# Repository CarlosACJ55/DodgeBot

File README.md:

# DodgeBot

<!--  -->
## Youtube Demo Video Links

## Description

Punch-dodging robot project started as a senior design group project for ECE 47700 group 5 at Purdue University.

<!-- ### Project Website

Learn about PunchBot on our Project Website!
Https://engineering.purdue.edu/477grp5/ -->

### Dependencies

* Brains coded in Python 3
  - Packaged with **Poetry**
  - Developped with **Pytest**
  - Ui designed in **tkinter**
* Braum controlled by **STM32F7** programmed in **C**
  - Generated drivers with **STM32CubeMX**
  - Depelopped for **Yaskawa** **SGM7G-30A** & **SGM7G-20A** motors

## Authors

* Yusuf Jarada
* Maximillian Drach
* Ayman Motoda
* Carlos Cotera

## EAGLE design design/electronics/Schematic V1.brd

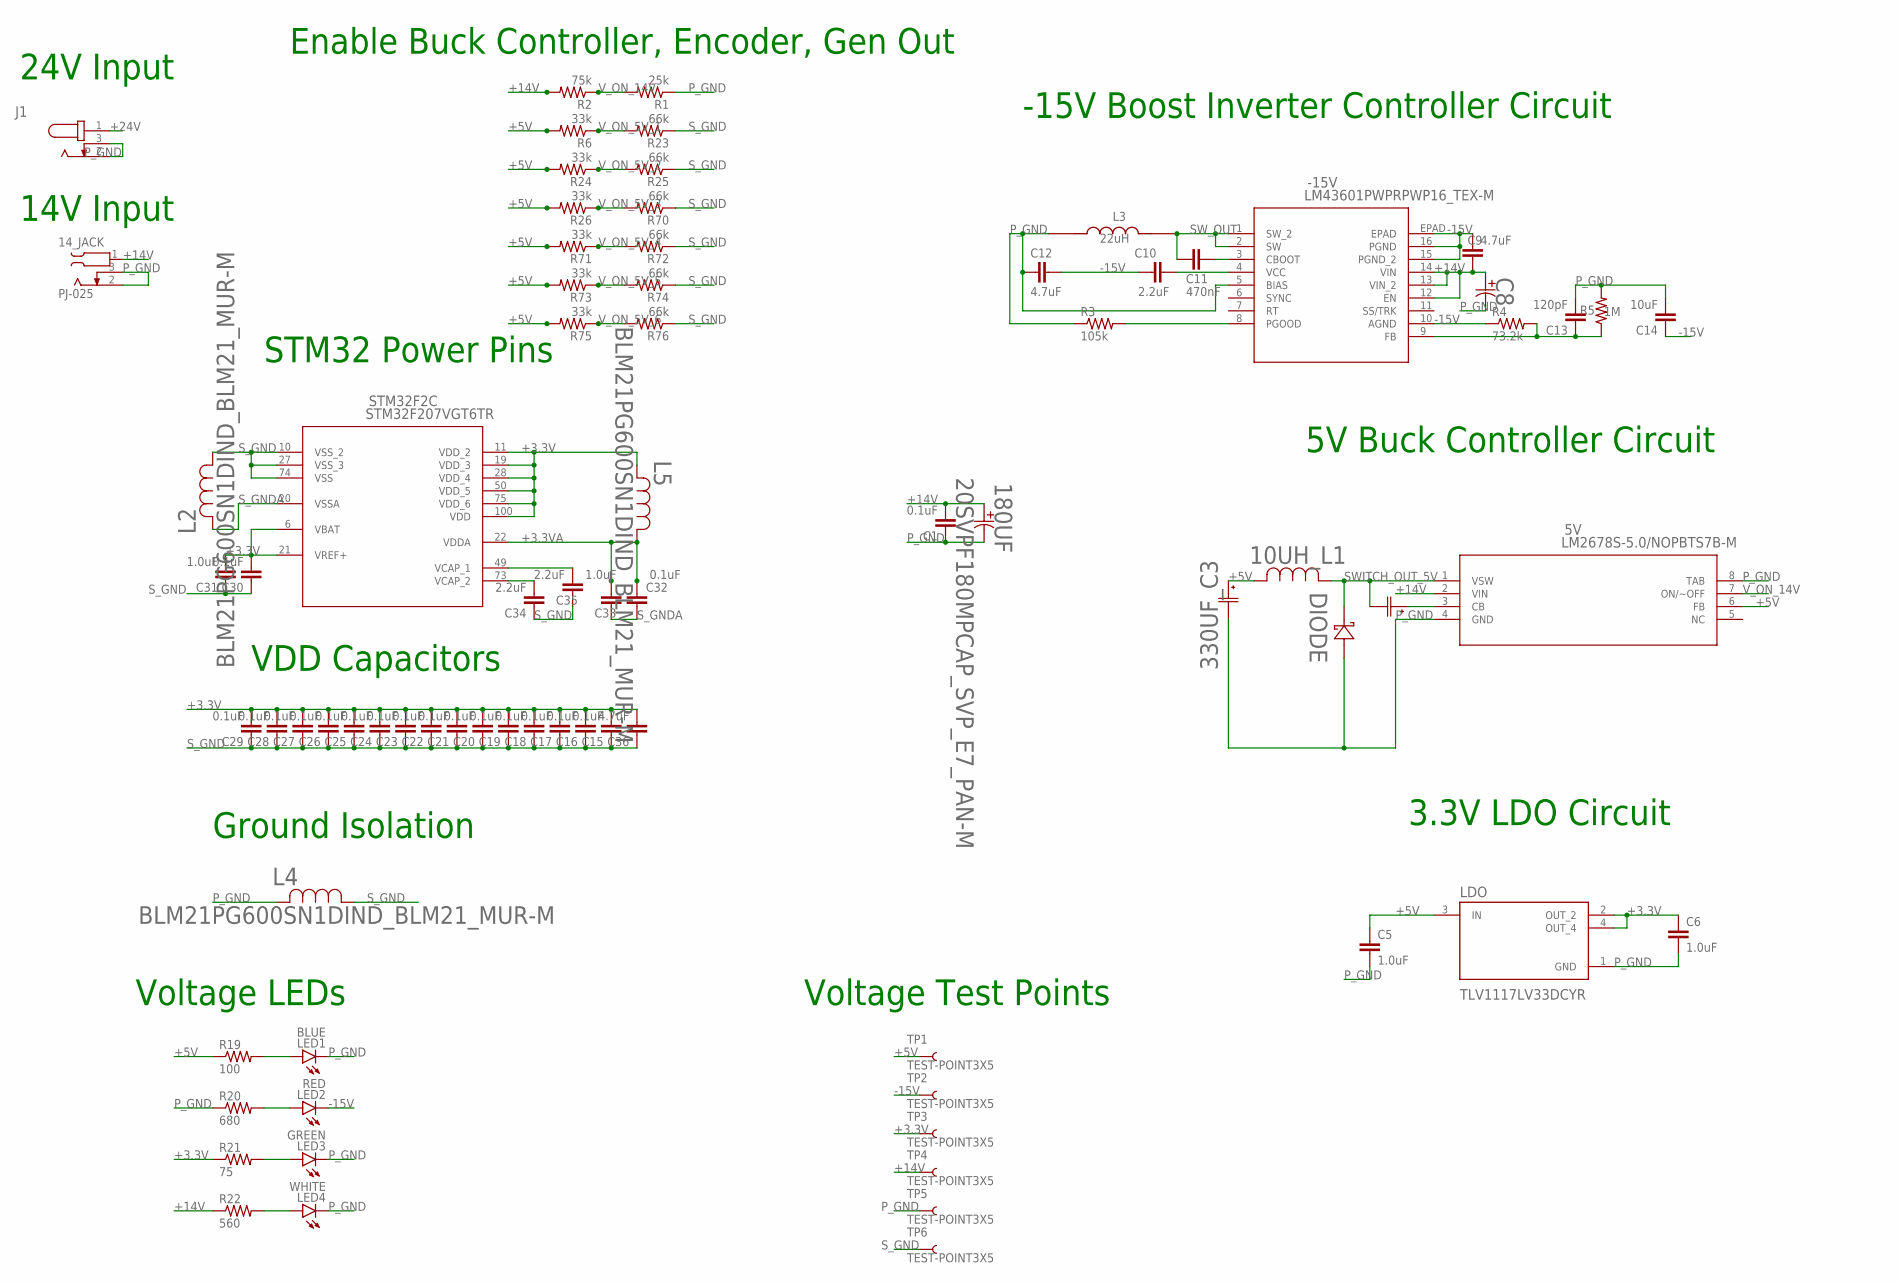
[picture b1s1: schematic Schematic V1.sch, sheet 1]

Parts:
0.01UF_C7: GRM2195C1H103JA01DG-21_MUR-M; G-21_MUR-M
5V: LM2678S-5.0/NOPBTS7B-M; TS7B-M
10UH_L1: SRP1270-100MIND_BOURNS_SRP1270-M; IND_BOURNS_SRP1270-M
14_JACK: PJ-025; CUI_PJ-025
180UF: 20SVPF180MPCAP_SVP_E7_PAN-M; PCAP_SVP_E7_PAN-M
330UF_C3: 10SVPC330MCAP_SVPC_E7_PAN-M; CAP_SVPC_E7_PAN-M
-15V: LM43601PWPRPWP16_TEX-M; PWP16_TEX-M
C1, C15, C16, C17, C18, C19, C20, C21, C22, C23, C24, C25, C26, C27, C28, C29, C30, C32: 0.1uF; 0805
C5, C6, C31, C33: 1.0uF; 0805
C8: 68uF; PCAP_6.3X7.7-ELECT_NCA-M
C9, C12, C36: 4.7uF; 0805
C10, C34, C35: 2.2uF; 0805
C11: 470nF; 0805
C13: 120pF; 0805
C14: 10uF; 0805
DIODE: CDBC520-GCDBC-G-M; CDBC-G-M
J1: PJ-202AH; CUI_PJ-202AH
L2, L4, L5: BLM21PG600SN1DIND_BLM21_MUR-M; IND_BLM21_MUR-M
L3: 22uH; IND_VLS201610CX-220M-1
LDO: TLV1117LV33DCYR; VREG_TLV1117LV33DCYR
LED1: BLUE; CHIPLED_0805
LED2: RED; CHIPLED_0805
LED3: GREEN; CHIPLED_0805
LED4: WHITE; CHIPLED_0805
R1: 25k; R0805
R2: 75k; R0805
R3: 105k; R0805
R4: 73.2k; R0805
R5: 1M; R0805
R6, R24, R26, R71, R73, R75: 33k; R0805
R19: 100; R0805
R20: 680; R0805
R21: 75; R0805
R22: 560; R0805
R23, R25, R70, R72, R74, R76: 66k; R0805
STM32F2: STM32F207VGT6TR; LQFP100-14X14MM
TP1, TP2, TP3, TP4, TP5, TP6: TEST-POINT3X5; PAD.03X.05

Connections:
+3.3V: C6.1, C15.2, C16.2, C17.2, C18.2, C19.2, C20.2, C21.2, C22.2, C23.2, C24.2, C25.2, C26.2, C27.2, C28.2, C29.2, C30.2, C31.2, C36.2, L5.2, LDO.2 (OUT_2), LDO.4 (OUT_4), R21.1, STM32F2.6 (VBAT), STM32F2.11 (VDD_2), STM32F2.19 (VDD_3), STM32F2.21 (VREF+), STM32F2.28 (VDD_4), STM32F2.50 (VDD_5), STM32F2.75 (VDD_6), STM32F2.100 (VDD), TP3.1; also elsewhere on the board
+3.3VA: C32.2, C33.2, L5.1, STM32F2.22 (VDDA)
+5V: 5V.6 (FB), 10UH_L1.2, 330UF_C3.1, C5.1, LDO.3 (IN), R6.2, R19.1, R24.2, R26.2, R71.2, R73.2, R75.2, TP1.1; also elsewhere on the board
+14V: 5V.2 (VIN), 14_JACK.1, 180UF.1, -15V.12 (EN), -15V.13 (VIN_2), -15V.14 (VIN), C1.2, C8.1, C9.2, R2.2, R22.1, TP4.1; also elsewhere on the board
+24V: J1.1; also elsewhere on the board
-15V: -15V.10 (AGND), -15V.15 (PGND_2), -15V.16 (PGND), -15V.EPAD, C9.1, C10.1, C12.1, C14.1, LED2.C, R4.1, TP2.1; also elsewhere on the board
unnamed: -15V.4 (VCC), C10.2
unnamed: 0.01UF_C7.1, 5V.3 (CB)
unnamed: -15V.3 (CBOOT), C11.2
unnamed: C35.2, STM32F2.49 (VCAP_1)
unnamed: C34.2, STM32F2.73 (VCAP_2)
unnamed: -15V.8 (PGOOD), R3.2
unnamed: -15V.9 (FB), C13.1, R4.2, R5.1
unnamed: LED1.A, R19.2
unnamed: LED2.A, R20.2
unnamed: LED3.A, R21.2
unnamed: LED4.A, R22.2
P_GND: 5V.4 (GND), 5V.8 (TAB), 14_JACK.2, 14_JACK.3, 180UF.2, 330UF_C3.2, -15V.5 (BIAS), C1.1, C5.2, C6.2, C8.2, C12.2, C13.2, C14.2, DIODE.2, J1.2, J1.3, L3.1, L4.2, LDO.1 (GND), LED1.C, LED3.C, LED4.C, R1.1, R3.1, R5.2, R20.1, TP5.1; also elsewhere on the board
SWITCH_OUT_5V: 0.01UF_C7.2, 5V.1 (VSW), 10UH_L1.1, DIODE.1
SW_OUT: -15V.1 (SW_2), -15V.2 (SW), C11.1, L3.2
S_GND: C15.1, C16.1, C17.1, C18.1, C19.1, C20.1, C21.1, C22.1, C23.1, C24.1, C25.1, C26.1, C27.1, C28.1, C29.1, C30.1, C31.1, C34.1, C35.1, C36.1, L2.1, L4.1, R23.1, R25.1, R70.1, R72.1, R74.1, R76.1, STM32F2.10 (VSS_2), STM32F2.27 (VSS_3), STM32F2.74 (VSS), TP6.1; also elsewhere on the board
S_GNDA: C32.1, C33.1, L2.2, STM32F2.20 (VSSA)
V_ON_5V_1: R6.1, R23.2; also elsewhere on the board
V_ON_5V_2: R24.1, R25.2; also elsewhere on the board
V_ON_5V_3: R26.1, R70.2; also elsewhere on the board
V_ON_5V_4: R71.1, R72.2; also elsewhere on the board
V_ON_5V_5: R73.1, R74.2; also elsewhere on the board
V_ON_5V_6: R75.1, R76.2; also elsewhere on the board
V_ON_14V: 5V.7 (ON/~OFF), R1.2, R2.1

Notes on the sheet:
VDD Capacitors
STM32 Power Pins
5V Buck Controller Circuit
3.3V LDO Circuit
-15V Boost Inverter Controller Circuit
Enable Buck Controller, Encoder, Gen Out
Ground Isolation
Voltage LEDs
Voltage Test Points
14V Input
24V Input

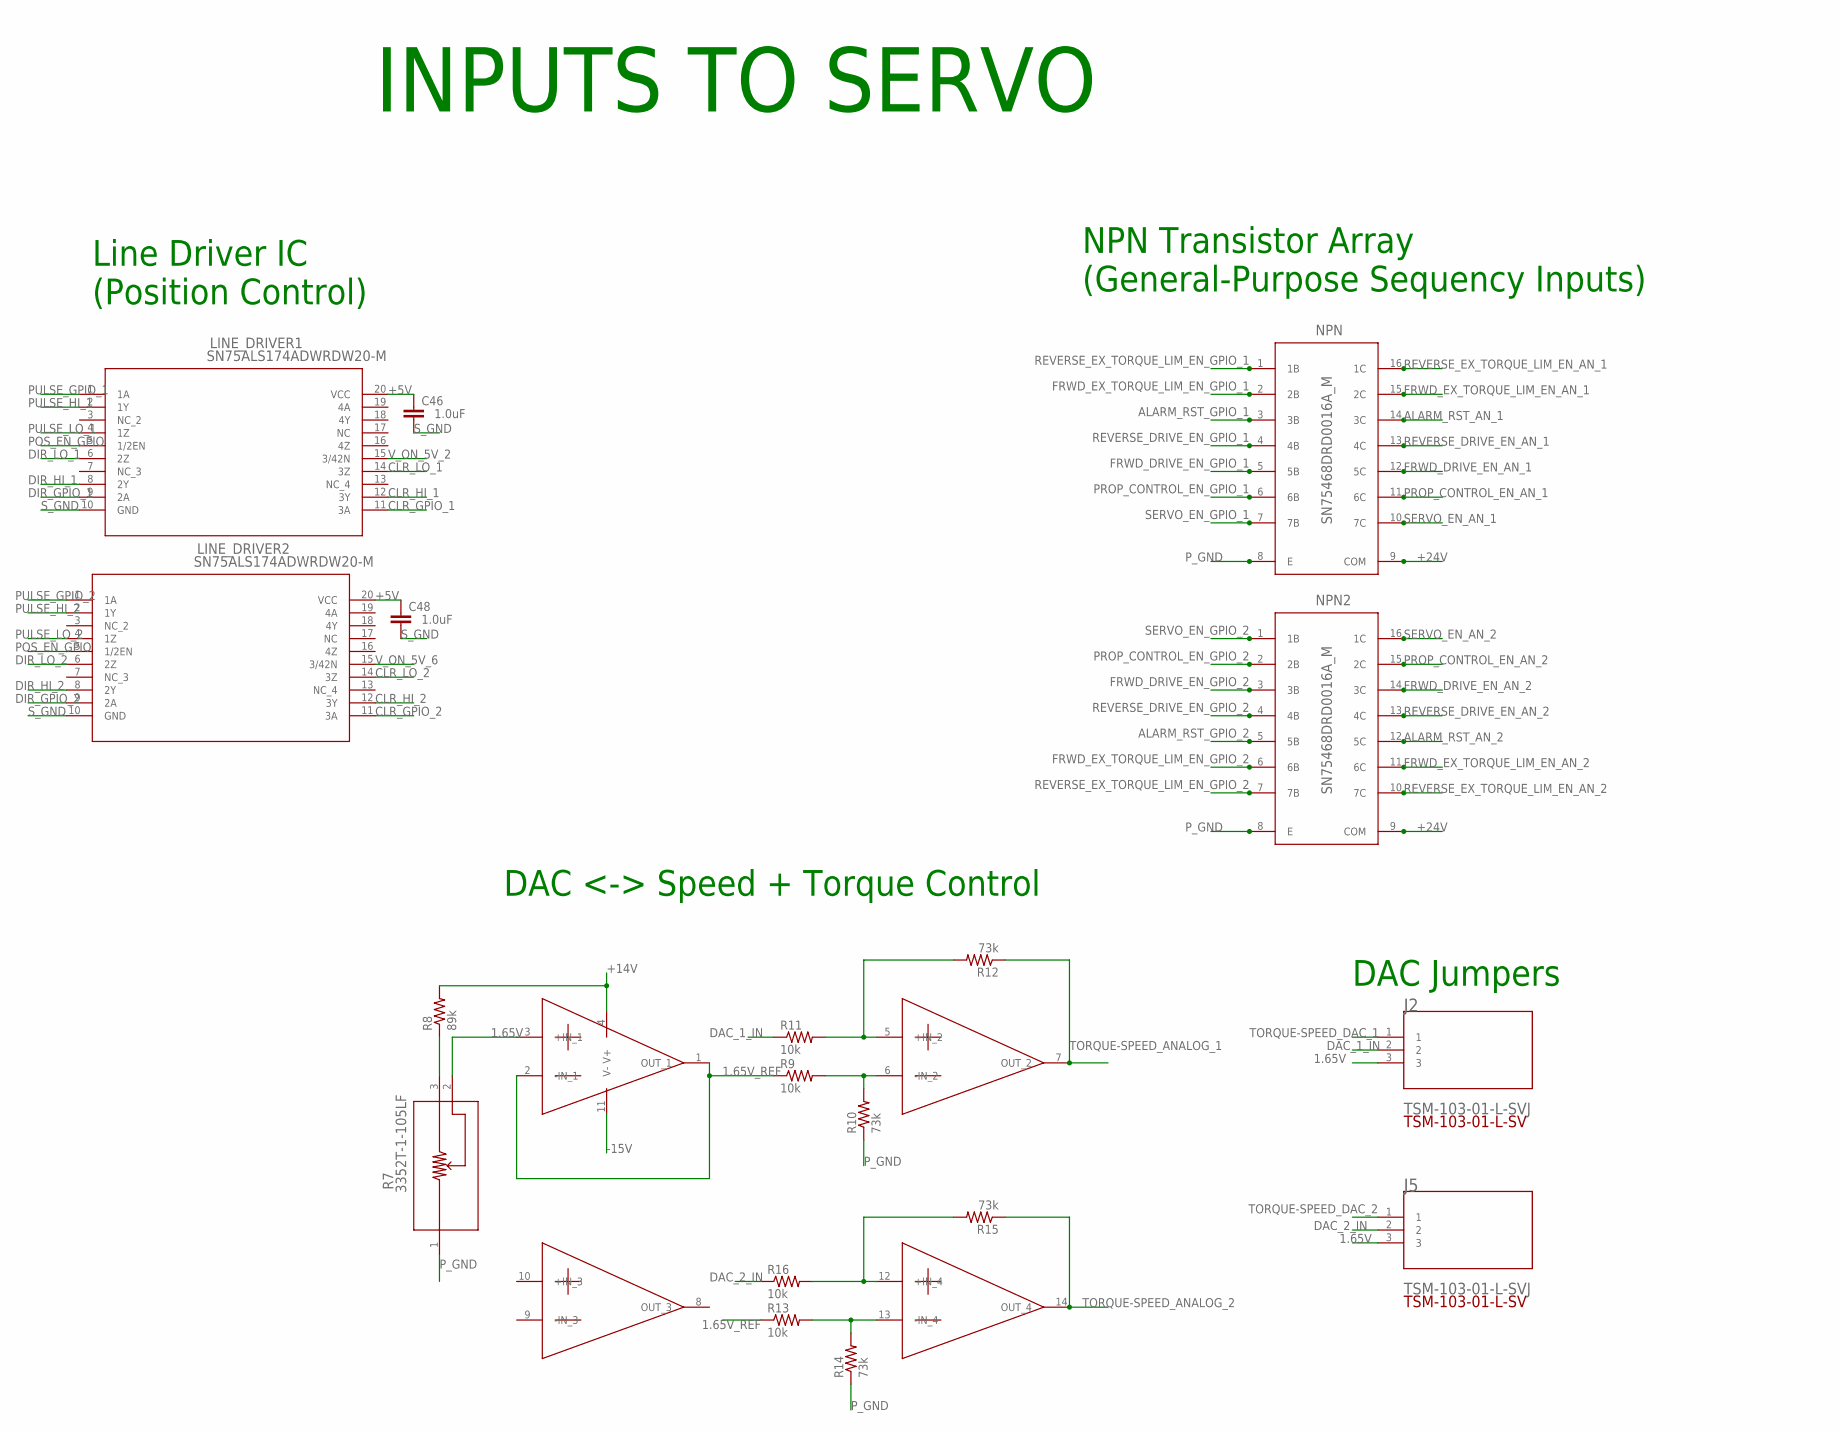
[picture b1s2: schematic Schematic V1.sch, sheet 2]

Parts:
C46, C48: 1.0uF; 0805
J2, J5: TSM-103-01-L-SVJ; TSM-103-01-L-SV
LINE_DRIVER1, LINE_DRIVER2: SN75ALS174ADWRDW20-M; DW20-M
NPN, NPN2: SN75468DRD0016A_M; D0016A_M
OP_AMP: OPA4205APWRTSSOP14_PW_R-PDSO-G14_TEX-M; TSSOP14_PW_R-PDSO-G14_TEX-M
R7: 3352T-1-105LF; 3352T_BRN
R8: 89k; R0805
R9, R11, R13, R16: 10k; R0805
R10, R12, R14, R15: 73k; R0805

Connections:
1.65V: J2.3, J5.3, OP_AMP.3 (+IN_1), R7.2
1.65V_REF: OP_AMP.1 (OUT_1), OP_AMP.2 (-IN_1), R9.1, R13.1
+5V: C46.2, C48.2, LINE_DRIVER1.20 (VCC), LINE_DRIVER2.20 (VCC); also elsewhere on the board
+14V: OP_AMP.4 (V+), R8.2; also elsewhere on the board
+24V: NPN.9 (COM), NPN2.9 (COM); also elsewhere on the board
-15V: OP_AMP.11 (V-); also elsewhere on the board
ALARM_RST_AN_1: NPN.14 (3C); also elsewhere on the board
ALARM_RST_AN_2: NPN2.12 (5C); also elsewhere on the board
ALARM_RST_GPIO_1: NPN.3 (3B); also elsewhere on the board
ALARM_RST_GPIO_2: NPN2.5 (5B); also elsewhere on the board
CLR_GPIO_1: LINE_DRIVER1.11 (3A); also elsewhere on the board
CLR_GPIO_2: LINE_DRIVER2.11 (3A); also elsewhere on the board
CLR_HI_1: LINE_DRIVER1.12 (3Y); also elsewhere on the board
CLR_HI_2: LINE_DRIVER2.12 (3Y); also elsewhere on the board
CLR_LO_1: LINE_DRIVER1.14 (3Z); also elsewhere on the board
CLR_LO_2: LINE_DRIVER2.14 (3Z); also elsewhere on the board
DAC_1_IN: J2.2, R11.1
DAC_2_IN: J5.2, R16.1
DIR_GPIO_1: LINE_DRIVER1.9 (2A); also elsewhere on the board
DIR_GPIO_2: LINE_DRIVER2.9 (2A); also elsewhere on the board
DIR_HI_1: LINE_DRIVER1.8 (2Y); also elsewhere on the board
DIR_HI_2: LINE_DRIVER2.8 (2Y); also elsewhere on the board
DIR_LO_1: LINE_DRIVER1.6 (2Z); also elsewhere on the board
DIR_LO_2: LINE_DRIVER2.6 (2Z); also elsewhere on the board
FRWD_DRIVE_EN_AN_1: NPN.12 (5C); also elsewhere on the board
FRWD_DRIVE_EN_AN_2: NPN2.14 (3C); also elsewhere on the board
FRWD_DRIVE_EN_GPIO_1: NPN.5 (5B); also elsewhere on the board
FRWD_DRIVE_EN_GPIO_2: NPN2.3 (3B); also elsewhere on the board
FRWD_EX_TORQUE_LIM_EN_AN_1: NPN.15 (2C); also elsewhere on the board
FRWD_EX_TORQUE_LIM_EN_AN_2: NPN2.11 (6C); also elsewhere on the board
FRWD_EX_TORQUE_LIM_EN_GPIO_1: NPN.2 (2B); also elsewhere on the board
FRWD_EX_TORQUE_LIM_EN_GPIO_2: NPN2.6 (6B); also elsewhere on the board
unnamed: OP_AMP.6 (-IN_2), R9.2, R10.2
unnamed: R7.3, R8.1
unnamed: OP_AMP.5 (+IN_2), R11.2, R12.2
unnamed: OP_AMP.13 (-IN_4), R13.2, R14.2
unnamed: OP_AMP.12 (+IN_4), R15.2, R16.2
POS_EN_GPIO: LINE_DRIVER1.5 (1/2EN), LINE_DRIVER2.5 (1/2EN); also elsewhere on the board
PROP_CONTROL_EN_AN_1: NPN.11 (6C); also elsewhere on the board
PROP_CONTROL_EN_AN_2: NPN2.15 (2C); also elsewhere on the board
PROP_CONTROL_EN_GPIO_1: NPN.6 (6B); also elsewhere on the board
PROP_CONTROL_EN_GPIO_2: NPN2.2 (2B); also elsewhere on the board
PULSE_GPIO_1: LINE_DRIVER1.1 (1A); also elsewhere on the board
PULSE_GPIO_2: LINE_DRIVER2.1 (1A); also elsewhere on the board
PULSE_HI_1: LINE_DRIVER1.2 (1Y); also elsewhere on the board
PULSE_HI_2: LINE_DRIVER2.2 (1Y); also elsewhere on the board
PULSE_LO_1: LINE_DRIVER1.4 (1Z); also elsewhere on the board
PULSE_LO_2: LINE_DRIVER2.4 (1Z); also elsewhere on the board
P_GND: NPN.8 (E), NPN2.8 (E), R7.1, R10.1, R14.1; also elsewhere on the board
REVERSE_DRIVE_EN_AN_1: NPN.13 (4C); also elsewhere on the board
REVERSE_DRIVE_EN_AN_2: NPN2.13 (4C); also elsewhere on the board
REVERSE_DRIVE_EN_GPIO_1: NPN.4 (4B); also elsewhere on the board
REVERSE_DRIVE_EN_GPIO_2: NPN2.4 (4B); also elsewhere on the board
REVERSE_EX_TORQUE_LIM_EN_AN_1: NPN.16 (1C); also elsewhere on the board
REVERSE_EX_TORQUE_LIM_EN_AN_2: NPN2.10 (7C); also elsewhere on the board
REVERSE_EX_TORQUE_LIM_EN_GPIO_1: NPN.1 (1B); also elsewhere on the board
REVERSE_EX_TORQUE_LIM_EN_GPIO_2: NPN2.7 (7B); also elsewhere on the board
SERVO_EN_AN_1: NPN.10 (7C); also elsewhere on the board
SERVO_EN_AN_2: NPN2.16 (1C); also elsewhere on the board
SERVO_EN_GPIO_1: NPN.7 (7B); also elsewhere on the board
SERVO_EN_GPIO_2: NPN2.1 (1B); also elsewhere on the board
S_GND: C46.1, C48.1, LINE_DRIVER1.10 (GND), LINE_DRIVER2.10 (GND); also elsewhere on the board
TORQUE-SPEED_ANALOG_1: OP_AMP.7 (OUT_2), R12.1; also elsewhere on the board
TORQUE-SPEED_ANALOG_2: OP_AMP.14 (OUT_4), R15.1; also elsewhere on the board
TORQUE-SPEED_DAC_1: J2.1; also elsewhere on the board
TORQUE-SPEED_DAC_2: J5.1; also elsewhere on the board
V_ON_5V_2: LINE_DRIVER1.15 (3/42N); also elsewhere on the board
V_ON_5V_6: LINE_DRIVER2.15 (3/42N); also elsewhere on the board

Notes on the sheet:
Line Driver IC (Position Control)
DAC <-> Speed + Torque Control
INPUTS TO SERVO
NPN Transistor Array (General-Purpose Sequency Inputs)
DAC Jumpers

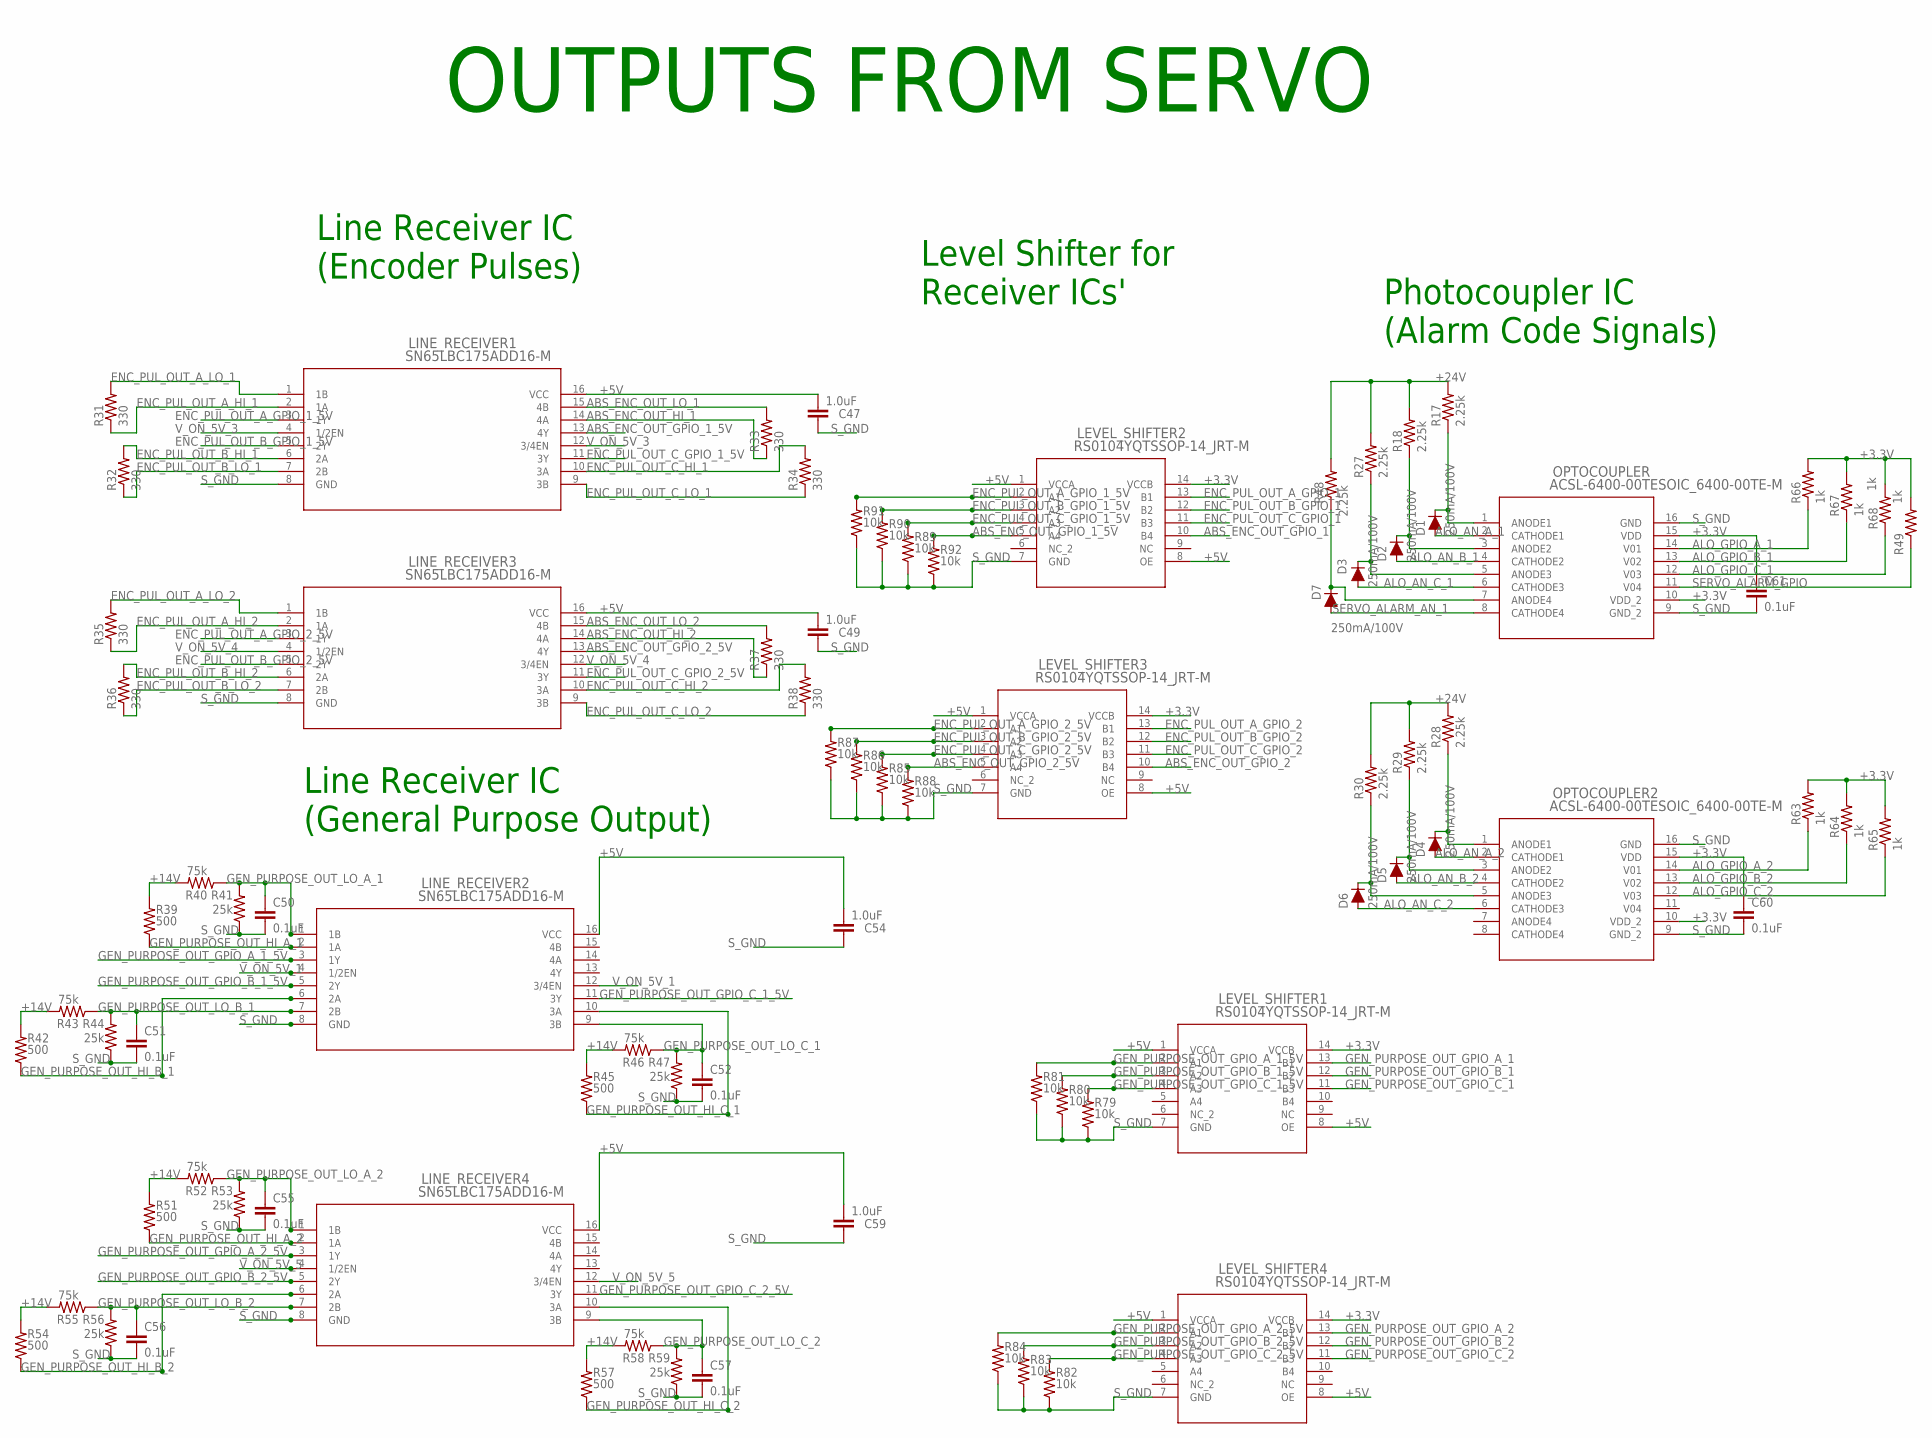
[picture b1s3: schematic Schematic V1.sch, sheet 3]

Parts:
C47, C49, C54, C59: 1.0uF; 0805
C50, C51, C52, C55, C56, C57, C60, C61: 0.1uF; 0805
D1, D2, D3, D4, D5, D6, D7: 250mA/100V; SOD-323
LEVEL_SHIFTER1, LEVEL_SHIFTER2, LEVEL_SHIFTER3, LEVEL_SHIFTER4: RS0104YQTSSOP-14_JRT-M; TSSOP-14_JRT-M
LINE_RECEIVER1, LINE_RECEIVER2, LINE_RECEIVER3, LINE_RECEIVER4: SN65LBC175ADD16-M; D16-M
OPTOCOUPLER, OPTOCOUPLER2: ACSL-6400-00TESOIC_6400-00TE-M; SOIC_6400-00TE-M
R17, R18, R27, R28, R29, R30, R48: 2.25k; R0805
R31, R32, R33, R34, R35, R36, R37, R38: 330; R0805
R39, R42, R45, R51, R54, R57: 500; R0805
R40, R43, R46, R52, R55, R58: 75k; R0805
R41, R44, R47, R53, R56, R59: 25k; R0805
R49, R63, R64, R65, R66, R67, R68: 1k; R0805
R79, R80, R81, R82, R83, R84, R85, R86, R87, R88, R89, R90, R91, R92: 10k; R0805

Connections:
+3.3V: C60.2, C61.2, LEVEL_SHIFTER1.14 (VCCB), LEVEL_SHIFTER2.14 (VCCB), LEVEL_SHIFTER3.14 (VCCB), LEVEL_SHIFTER4.14 (VCCB), OPTOCOUPLER.10 (VDD_2), OPTOCOUPLER.15 (VDD), OPTOCOUPLER2.10 (VDD_2), OPTOCOUPLER2.15 (VDD), R49.2, R63.2, R64.2, R65.2, R66.2, R67.2, R68.2; also elsewhere on the board
+5V: C47.2, C49.2, C54.2, C59.2, LEVEL_SHIFTER1.1 (VCCA), LEVEL_SHIFTER1.8 (OE), LEVEL_SHIFTER2.1 (VCCA), LEVEL_SHIFTER2.8 (OE), LEVEL_SHIFTER3.1 (VCCA), LEVEL_SHIFTER3.8 (OE), LEVEL_SHIFTER4.1 (VCCA), LEVEL_SHIFTER4.8 (OE), LINE_RECEIVER1.16 (VCC), LINE_RECEIVER2.16 (VCC), LINE_RECEIVER3.16 (VCC), LINE_RECEIVER4.16 (VCC); also elsewhere on the board
+14V: R39.2, R40.2, R42.2, R43.2, R45.2, R46.2, R51.2, R52.2, R54.2, R55.2, R57.2, R58.2; also elsewhere on the board
+24V: R17.2, R18.2, R27.2, R28.2, R29.2, R30.2, R48.2; also elsewhere on the board
ABS_ENC_OUT_GPIO_1: LEVEL_SHIFTER2.10 (B4); also elsewhere on the board
ABS_ENC_OUT_GPIO_1_5V: LEVEL_SHIFTER2.5 (A4), LINE_RECEIVER1.13 (4Y), R92.2
ABS_ENC_OUT_GPIO_2: LEVEL_SHIFTER3.10 (B4); also elsewhere on the board
ABS_ENC_OUT_GPIO_2_5V: LEVEL_SHIFTER3.5 (A4), LINE_RECEIVER3.13 (4Y), R88.2
ABS_ENC_OUT_HI_1: LINE_RECEIVER1.14 (4A), R33.1; also elsewhere on the board
ABS_ENC_OUT_HI_2: LINE_RECEIVER3.14 (4A), R37.1; also elsewhere on the board
ABS_ENC_OUT_LO_1: LINE_RECEIVER1.15 (4B), R33.2; also elsewhere on the board
ABS_ENC_OUT_LO_2: LINE_RECEIVER3.15 (4B), R37.2; also elsewhere on the board
ALO_AN_A_1: D1.A, OPTOCOUPLER.2 (CATHODE1); also elsewhere on the board
ALO_AN_A_2: D4.A, OPTOCOUPLER2.2 (CATHODE1); also elsewhere on the board
ALO_AN_B_1: D2.A, OPTOCOUPLER.4 (CATHODE2); also elsewhere on the board
ALO_AN_B_2: D5.A, OPTOCOUPLER2.4 (CATHODE2); also elsewhere on the board
ALO_AN_C_1: D3.A, OPTOCOUPLER.6 (CATHODE3); also elsewhere on the board
ALO_AN_C_2: D6.A, OPTOCOUPLER2.6 (CATHODE3); also elsewhere on the board
ALO_GPIO_A_1: OPTOCOUPLER.14 (V01), R66.1; also elsewhere on the board
ALO_GPIO_A_2: OPTOCOUPLER2.14 (V01), R63.1; also elsewhere on the board
ALO_GPIO_B_1: OPTOCOUPLER.13 (V02), R67.1; also elsewhere on the board
ALO_GPIO_B_2: OPTOCOUPLER2.13 (V02), R64.1; also elsewhere on the board
ALO_GPIO_C_1: OPTOCOUPLER.12 (V03), R68.1; also elsewhere on the board
ALO_GPIO_C_2: OPTOCOUPLER2.12 (V03), R65.1; also elsewhere on the board
ENC_PUL_OUT_A_GPIO_1: LEVEL_SHIFTER2.13 (B1); also elsewhere on the board
ENC_PUL_OUT_A_GPIO_1_5V: LEVEL_SHIFTER2.2 (A1), LINE_RECEIVER1.3 (1Y), R91.2
ENC_PUL_OUT_A_GPIO_2: LEVEL_SHIFTER3.13 (B1); also elsewhere on the board
ENC_PUL_OUT_A_GPIO_2_5V: LEVEL_SHIFTER3.2 (A1), LINE_RECEIVER3.3 (1Y), R87.2
ENC_PUL_OUT_A_HI_1: LINE_RECEIVER1.2 (1A), R31.1; also elsewhere on the board
ENC_PUL_OUT_A_HI_2: LINE_RECEIVER3.2 (1A), R35.1; also elsewhere on the board
ENC_PUL_OUT_A_LO_1: LINE_RECEIVER1.1 (1B), R31.2; also elsewhere on the board
ENC_PUL_OUT_A_LO_2: LINE_RECEIVER3.1 (1B), R35.2; also elsewhere on the board
ENC_PUL_OUT_B_GPIO_1: LEVEL_SHIFTER2.12 (B2); also elsewhere on the board
ENC_PUL_OUT_B_GPIO_1_5V: LEVEL_SHIFTER2.3 (A2), LINE_RECEIVER1.5 (2Y), R90.2
ENC_PUL_OUT_B_GPIO_2: LEVEL_SHIFTER3.12 (B2); also elsewhere on the board
ENC_PUL_OUT_B_GPIO_2_5V: LEVEL_SHIFTER3.3 (A2), LINE_RECEIVER3.5 (2Y), R86.2
ENC_PUL_OUT_B_HI_1: LINE_RECEIVER1.6 (2A), R32.2; also elsewhere on the board
ENC_PUL_OUT_B_HI_2: LINE_RECEIVER3.6 (2A), R36.2; also elsewhere on the board
ENC_PUL_OUT_B_LO_1: LINE_RECEIVER1.7 (2B), R32.1; also elsewhere on the board
ENC_PUL_OUT_B_LO_2: LINE_RECEIVER3.7 (2B), R36.1; also elsewhere on the board
ENC_PUL_OUT_C_GPIO_1: LEVEL_SHIFTER2.11 (B3); also elsewhere on the board
ENC_PUL_OUT_C_GPIO_1_5V: LEVEL_SHIFTER2.4 (A3), LINE_RECEIVER1.11 (3Y), R89.2
ENC_PUL_OUT_C_GPIO_2: LEVEL_SHIFTER3.11 (B3); also elsewhere on the board
ENC_PUL_OUT_C_GPIO_2_5V: LEVEL_SHIFTER3.4 (A3), LINE_RECEIVER3.11 (3Y), R85.2
ENC_PUL_OUT_C_HI_1: LINE_RECEIVER1.10 (3A), R34.2; also elsewhere on the board
ENC_PUL_OUT_C_HI_2: LINE_RECEIVER3.10 (3A), R38.2; also elsewhere on the board
ENC_PUL_OUT_C_LO_1: LINE_RECEIVER1.9 (3B), R34.1; also elsewhere on the board
ENC_PUL_OUT_C_LO_2: LINE_RECEIVER3.9 (3B), R38.1; also elsewhere on the board
GEN_PURPOSE_OUT_GPIO_A_1: LEVEL_SHIFTER1.13 (B1); also elsewhere on the board
GEN_PURPOSE_OUT_GPIO_A_1_5V: LEVEL_SHIFTER1.2 (A1), LINE_RECEIVER2.3 (1Y), R81.2
GEN_PURPOSE_OUT_GPIO_A_2: LEVEL_SHIFTER4.13 (B1); also elsewhere on the board
GEN_PURPOSE_OUT_GPIO_A_2_5V: LEVEL_SHIFTER4.2 (A1), LINE_RECEIVER4.3 (1Y), R84.2
GEN_PURPOSE_OUT_GPIO_B_1: LEVEL_SHIFTER1.12 (B2); also elsewhere on the board
GEN_PURPOSE_OUT_GPIO_B_1_5V: LEVEL_SHIFTER1.3 (A2), LINE_RECEIVER2.5 (2Y), R80.2
GEN_PURPOSE_OUT_GPIO_B_2: LEVEL_SHIFTER4.12 (B2); also elsewhere on the board
GEN_PURPOSE_OUT_GPIO_B_2_5V: LEVEL_SHIFTER4.3 (A2), LINE_RECEIVER4.5 (2Y), R83.2
GEN_PURPOSE_OUT_GPIO_C_1: LEVEL_SHIFTER1.11 (B3); also elsewhere on the board
GEN_PURPOSE_OUT_GPIO_C_1_5V: LEVEL_SHIFTER1.4 (A3), LINE_RECEIVER2.11 (3Y), R79.2
GEN_PURPOSE_OUT_GPIO_C_2: LEVEL_SHIFTER4.11 (B3); also elsewhere on the board
GEN_PURPOSE_OUT_GPIO_C_2_5V: LEVEL_SHIFTER4.4 (A3), LINE_RECEIVER4.11 (3Y), R82.2
GEN_PURPOSE_OUT_HI_A_1: LINE_RECEIVER2.2 (1A), R39.1; also elsewhere on the board
GEN_PURPOSE_OUT_HI_A_2: LINE_RECEIVER4.2 (1A), R51.1; also elsewhere on the board
GEN_PURPOSE_OUT_HI_B_1: LINE_RECEIVER2.6 (2A), R42.1; also elsewhere on the board
GEN_PURPOSE_OUT_HI_B_2: LINE_RECEIVER4.6 (2A), R54.1; also elsewhere on the board
GEN_PURPOSE_OUT_HI_C_1: LINE_RECEIVER2.10 (3A), R45.1; also elsewhere on the board
GEN_PURPOSE_OUT_HI_C_2: LINE_RECEIVER4.10 (3A), R57.1; also elsewhere on the board
GEN_PURPOSE_OUT_LO_A_1: C50.2, LINE_RECEIVER2.1 (1B), R40.1, R41.2; also elsewhere on the board
GEN_PURPOSE_OUT_LO_A_2: C55.2, LINE_RECEIVER4.1 (1B), R52.1, R53.2; also elsewhere on the board
GEN_PURPOSE_OUT_LO_B_1: C51.2, LINE_RECEIVER2.7 (2B), R43.1, R44.2; also elsewhere on the board
GEN_PURPOSE_OUT_LO_B_2: C56.2, LINE_RECEIVER4.7 (2B), R55.1, R56.2; also elsewhere on the board
GEN_PURPOSE_OUT_LO_C_1: C52.2, LINE_RECEIVER2.9 (3B), R46.1, R47.2; also elsewhere on the board
GEN_PURPOSE_OUT_LO_C_2: C57.2, LINE_RECEIVER4.9 (3B), R58.1, R59.2; also elsewhere on the board
unnamed: D7.C, OPTOCOUPLER.7 (ANODE4), R48.1
unnamed: D1.C, OPTOCOUPLER.1 (ANODE1), R17.1
unnamed: D2.C, OPTOCOUPLER.3 (ANODE2), R18.1
unnamed: D3.C, OPTOCOUPLER.5 (ANODE3), R27.1
unnamed: D4.C, OPTOCOUPLER2.1 (ANODE1), R28.1
unnamed: D5.C, OPTOCOUPLER2.3 (ANODE2), R29.1
unnamed: D6.C, OPTOCOUPLER2.5 (ANODE3), R30.1
SERVO_ALARM_AN_1: D7.A, OPTOCOUPLER.8 (CATHODE4); also elsewhere on the board
SERVO_ALARM_GPIO: OPTOCOUPLER.11 (V04), R49.1; also elsewhere on the board
S_GND: C47.1, C49.1, C50.1, C51.1, C52.1, C54.1, C55.1, C56.1, C57.1, C59.1, C60.1, C61.1, LEVEL_SHIFTER1.7 (GND), LEVEL_SHIFTER2.7 (GND), LEVEL_SHIFTER3.7 (GND), LEVEL_SHIFTER4.7 (GND), LINE_RECEIVER1.8 (GND), LINE_RECEIVER2.8 (GND), LINE_RECEIVER3.8 (GND), LINE_RECEIVER4.8 (GND), OPTOCOUPLER.9 (GND_2), OPTOCOUPLER.16 (GND), OPTOCOUPLER2.9 (GND_2), OPTOCOUPLER2.16 (GND), R41.1, R44.1, R47.1, R53.1, R56.1, R59.1, R79.1, R80.1, R81.1, R82.1, R83.1, R84.1, R85.1, R86.1, R87.1, R88.1, R89.1, R90.1, R91.1, R92.1; also elsewhere on the board
V_ON_5V_1: LINE_RECEIVER2.4 (1/2EN), LINE_RECEIVER2.12 (3/4EN); also elsewhere on the board
V_ON_5V_3: LINE_RECEIVER1.4 (1/2EN), LINE_RECEIVER1.12 (3/4EN); also elsewhere on the board
V_ON_5V_4: LINE_RECEIVER3.4 (1/2EN), LINE_RECEIVER3.12 (3/4EN); also elsewhere on the board
V_ON_5V_5: LINE_RECEIVER4.4 (1/2EN), LINE_RECEIVER4.12 (3/4EN); also elsewhere on the board

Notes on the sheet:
Line Receiver IC (Encoder Pulses)
OUTPUTS FROM SERVO
Photocoupler IC (Alarm Code Signals)
Line Receiver IC (General Purpose Output)
Level Shifter for Receiver ICs'

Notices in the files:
parts and their libraries:
SparkFun-Capacitors: Licensing: Creative Commons ShareAlike 4.0 International - https://creativecommons.org/licenses/by-sa/4.0
COPYRIGHT: Copyright (C) 2024 Ultra Librarian. All rights reserved.
